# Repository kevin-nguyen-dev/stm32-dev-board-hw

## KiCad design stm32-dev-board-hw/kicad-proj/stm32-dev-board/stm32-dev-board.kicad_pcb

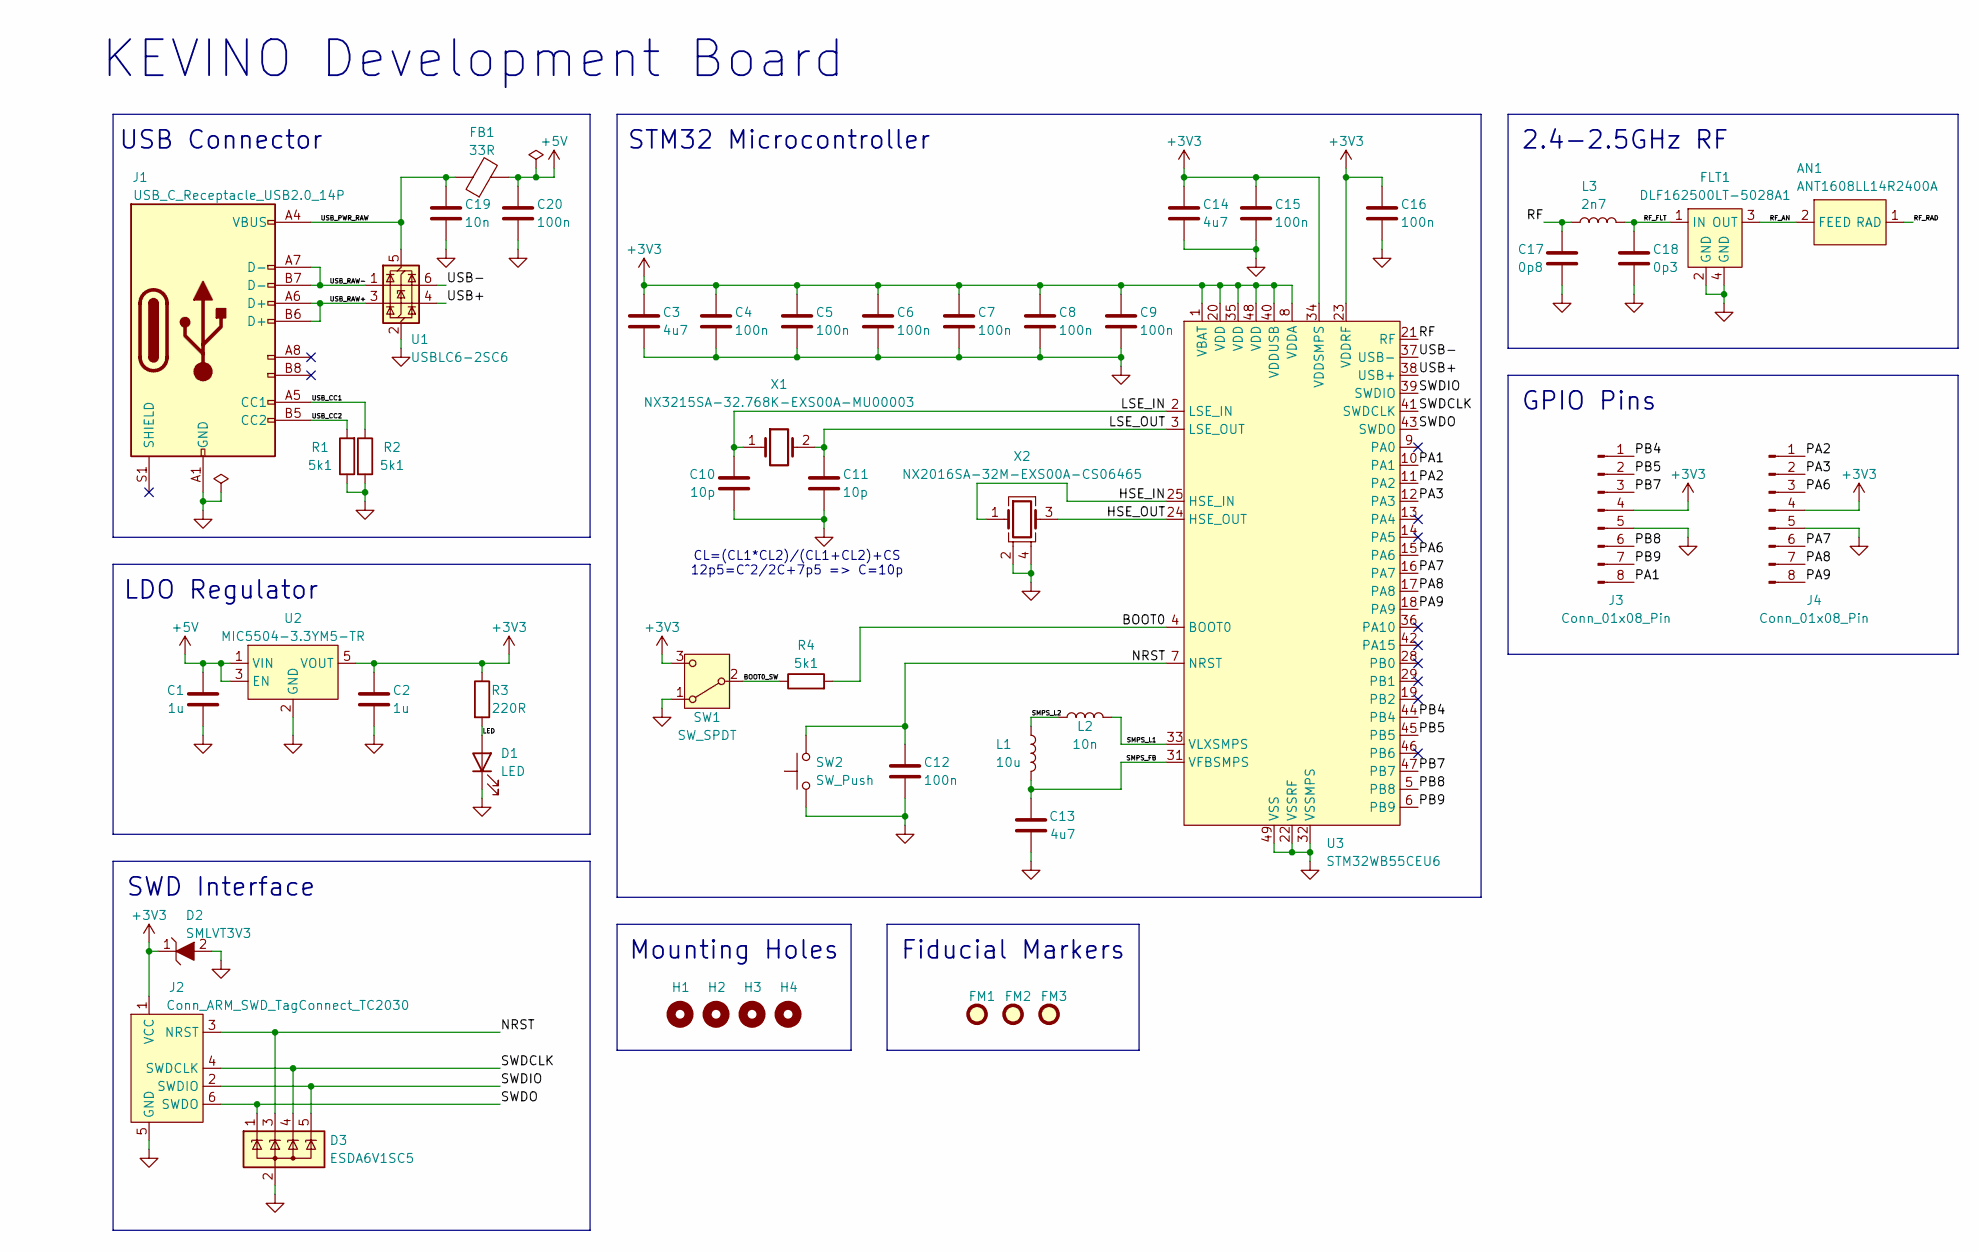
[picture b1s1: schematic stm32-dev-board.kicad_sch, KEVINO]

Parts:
AN1: ANT1608LL14R2400A; Manufacturer Part Number ANT1608LL14R2400A
C1, C2: 1u; C_0603_1608Metric; Manufacturer Part Number 0603ZD105KAT2A
C3, C13, C14: 4u7; C_0603_1608Metric; Manufacturer Part Number 0603YD475MAT2A
C4, C5, C6, C7, C8, C9, C12, C15, C16, C20: 100n; C_0402_1005Metric; Manufacturer Part Number 04023C104KAT2A
C10, C11: 10p; C_0402_1005Metric; Manufacturer Part Number 04025A100JAT2A
C17: 0p8; C_0402_1005Metric; Manufacturer Part Number GRM1555C1HR80BA01D
C18: 0p3; C_0402_1005Metric; Manufacturer Part Number GRM1555C1HR30WA01D
C19: 10n; C_0201_0603Metric; Manufacturer Part Number 0201ZC103JAT2A
D1: LED; LED_0402_1005Metric; Manufacturer Part Number 150040RS73240
D2: SMLVT3V3; Manufacturer Part Number SMLVT3V3
D3: ESDA6V1SC5; SOT-23-5; Manufacturer Part Number ESDA6V1SC5
FB1: 33R; R_0603_1608Metric; Manufacturer Part Number BLM18PG330SN1D
FLT1: DLF162500LT-5028A1; Manufacturer Part Number DLF162500LT-5028A1
FM1, FM2, FM3: Fiducial; Fiducial_1mm_Mask2mm
H1, H2, H3, H4: MountingHole; MountingHole_2.2mm_M2_DIN965_Pad
J1: USB_C_Receptacle_USB2.0_14P; USB_C_Receptacle_GCT_USB4105-xx-A_16P_TopMnt_Horizontal; Manufacturer Part Number USB4105-GF-A
J2: Conn_ARM_SWD_TagConnect_TC2030; Tag-Connect_TC2030-IDC-FP_2x03_P1.27mm_Vertical
J3, J4: Conn_01x08_Pin; PinHeader_1x08_P2.54mm_Vertical; Manufacturer Part Number 22-28-8082
L1: 10u; L_0805_2012Metric; Manufacturer Part Number LQM21FN100M70L
L2: 10n; L_0402_1005Metric; Manufacturer Part Number LQG15WZ10NJ02D
L3: 2n7; L_0402_1005Metric; Manufacturer Part Number LQG15HS2N7S02D
R1, R2, R4: 5k1; R_0402_1005Metric; Manufacturer Part Number RC0603FR-075K1L
R3: 220R; R_0402_1005Metric; Manufacturer Part Number RC0402FR-07221RL
SW1: SW_SPDT; SW_SPDT_PCM12; Manufacturer Part Number PCM12SMTR
SW2: SW_Push; SW_SPST_CK_RS282G05A3; Manufacturer Part Number RS282G05A3SMRT
U1: USBLC6-2SC6; SOT-23-6; Manufacturer Part Number USBLC6-2SC6
U2: MIC5504-3.3YM5-TR; SOT-23-5; Manufacturer Part Number MIC5504-3.3YM5-TR
U3: STM32WB55CEU6; Manufacturer Part Number STM32WB55CEU6
X1: NX3215SA-32.768K-EXS00A-MU00003; Crystal_SMD_MicroCrystal_CC7V-T1A-2Pin_3.2x1.5mm; Manufacturer Part Number NX3215SA-32.768K-EXS00A-MU00003
X2: NX2016SA-32M-EXS00A-CS06465; Crystal_SMD_2016-4Pin_2.0x1.6mm; Manufacturer Part Number NX2016SA-32M-EXS00A-CS06465

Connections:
+3V3: C2.1, C3.1, C4.1, C5.1, C6.1, C7.1, C8.1, C9.1, C14.1, C15.1, C16.1, D2.1, J2.1 (VCC), J3.4, J4.4, R3.1, SW1.3 (C), U2.5 (VOUT), U3.1 (VBAT), U3.8 (VDDA), U3.20 (VDD), U3.23 (VDDRF), U3.34 (VDDSMPS), U3.35 (VDD), U3.40 (VDDUSB), U3.48 (VDD)
+5V: C1.2, C20.1, FB1.2, U2.1 (VIN), U2.3 (EN)
/BOOT0: R4.2, U3.4 (BOOT0)
/BOOT0_SW: R4.1, SW1.2 (B)
/HSE_IN: U3.25 (HSE_IN), X2.1
/HSE_OUT: U3.24 (HSE_OUT), X2.3
/LED: D1.2 (A), R3.2
/LSE_IN: C10.2, U3.2 (LSE_IN), X1.1
/LSE_OUT: C11.1, U3.3 (LSE_OUT), X1.2
/NRST: C12.1, D3.3 (K), J2.3 (NRST), SW2.2, U3.7 (NRST)
/PA1: J3.8, U3.10 (PA1)
/PA2: J4.1, U3.11 (PA2)
/PA3: J4.2, U3.12 (PA3)
/PA6: J4.3, U3.15 (PA6)
/PA7: J4.6, U3.16 (PA7)
/PA8: J4.7, U3.17 (PA8)
/PA9: J4.8, U3.18 (PA9)
/PB4: J3.1, U3.44 (PB4)
/PB5: J3.2, U3.45 (PB5)
/PB7: J3.3, U3.47 (PB7)
/PB8: J3.6, U3.5 (PB8)
/PB9: J3.7, U3.6 (PB9)
/RF: C17.2, L3.1, U3.21 (RF)
/RF_AN: AN1.2 (FEED), FLT1.3 (OUT)
/RF_FLT: C18.1, FLT1.1 (IN), L3.2
/RF_RAD: AN1.1 (RAD)
/SMPS_FB: C13.2, L1.2, U3.31 (VFBSMPS)
/SMPS_L1: L2.2, U3.33 (VLXSMPS)
/SMPS_L2: L1.1, L2.1
/SWDCLK: D3.4 (K), J2.4 (SWDCLK), U3.41 (SWDCLK)
/SWDIO: D3.5 (K), J2.2 (SWDIO), U3.39 (SWDIO)
/SWDO: D3.1 (K), J2.6 (SWDO), U3.43 (SWDO)
/USB+: U1.4 (I/O2), U3.38 (USB+)
/USB-: U1.6 (I/O1), U3.37 (USB-)
/USB_CC1: J1.A5 (CC1), R2.1
/USB_CC2: J1.B5 (CC2), R1.2
/USB_PWR_RAW: C19.1, FB1.1, J1.A4 (VBUS), J1.A9 (VBUS), J1.B4 (VBUS), J1.B9 (VBUS), U1.5 (VBUS)
/USB_RAW+: J1.A6 (D+), J1.B6 (D+), U1.3 (I/O2)
/USB_RAW-: J1.A7 (D-), J1.B7 (D-), U1.1 (I/O1)
GND: C1.1, C2.2, C3.2, C4.2, C5.2, C6.2, C7.2, C8.2, C9.2, C10.1, C11.2, C12.2, C13.1, C14.2, C15.2, C16.2, C17.1, C18.2, C19.2, C20.2, D1.1 (K), D2.2, D3.2 (A), FLT1.2 (GND), FLT1.4 (GND), J1.A1 (GND), J1.A12 (GND), J1.B1 (GND), J1.B12 (GND), J2.5 (GND), J3.5, J4.5, R1.1, R2.2, SW1.1 (A), SW2.1, U1.2 (GND), U2.2 (GND), U3.22 (VSSRF), U3.32 (VSSMPS), U3.49 (VSS), X2.2, X2.4

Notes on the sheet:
KEVINO Development Board
2.4-2.5GHz RF
USB Connector
GPIO Pins
LDO Regulator
CL=(CL1*CL2)/(CL1+CL2)+CS 12p5=C^2/2C+7p5 => C=10p
Fiducial Markers
SWD Interface
STM32 Microcontroller
Mounting Holes

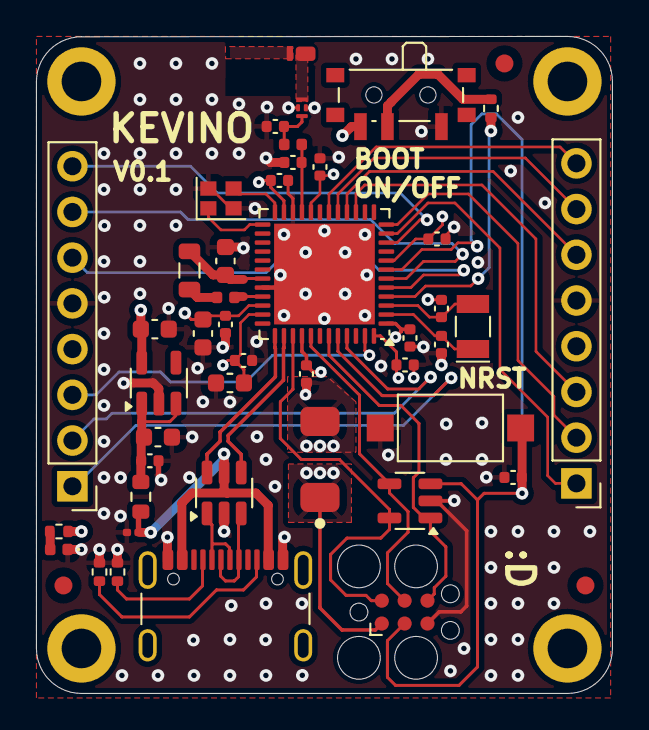
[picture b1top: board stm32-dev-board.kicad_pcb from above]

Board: 4 copper layers, 32.0 x 36.5 mm, 51 parts (0 on the bottom side), 39 nets.
